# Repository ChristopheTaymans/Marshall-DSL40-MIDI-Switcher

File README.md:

# MIDI switcher for Marshall DSL 40

## Introduction
This repository propose a DYI switcher for the Marshall DSL40 tube Amplificator. The switcher is capable to select channel 1 / 2 selection with switching between modes ( Clean/Crunch / OD1 /OD 2 ). It can select also Master 1 or 2 and the FX loop activation/deactivation.

The core of the circuit is an **Arduino Every**. 
The switcher is linked with the DSL40 through a MIDI cable ( DIN5 )  and is powered up with an external 9V source.
the switching command is provided by 4 momentary footswitches. 
- Footswitch 1 is for clean/crunch switching ( and implicitely for channel 1 activation): Two leds indicate the clean/crunch status
- Footswitch 2 is for OD1/OD2switching ( and implicitely for channel 2 activation ) : Two leds indicate the OD1/OD2 status
- Footswitch 3 is for Master 1 / Master 2 switching : Two leds indicate the Mastezr 1 / 2 status
- Footswitch 4 is FX loop activation/deactivation : one led indicates the FX loop status.

***Short demo video at https://youtu.be/Z-kX9PDRV-0***

## Synchronisation function

The "issue" with DSL40 is that there is no MIDI messages sent back by the amp. to the switcher to give the current status of all presets.
Each modes ( clean/crunch/OD1/OD2) have their own presets regarding FX loop and Master. Combination of presets might become a bit complex and lead to a de-synchronisation.
So, each time the switcher is turned on, the amp. preset must be manually synchronised with the switcher preset state ( leds ). Also, if a preset is modified manually during a use session, the switcher is desyncronised with the amp.
With most of the DYI switcher that I've seen on the web, the manual (re)synchronisation is a must to keep both switcher and amp. on the same state.

This switcher program have an integrated syncrhonisation function. The switcher presets states are stored in the EEPROM. So, each time the switcher is turned on, its last state is restored. 
if the amp presets has been modified manually in the mean time, a synchronisation of the amps can be triggered by a long hold ( > 3 sec. ) on the clean/crunch footswitch.

In a first version of the program, the synchronisation was triggered each time the switcher was turned on. Finally, the synchro is only triggered by demand.

## Hardware 

In the folder Eagle, you'll find schematic and board implementation to build the circuit board. 
If you have a CNC machine, you'll find the G code files to engrave the circuit and the case.

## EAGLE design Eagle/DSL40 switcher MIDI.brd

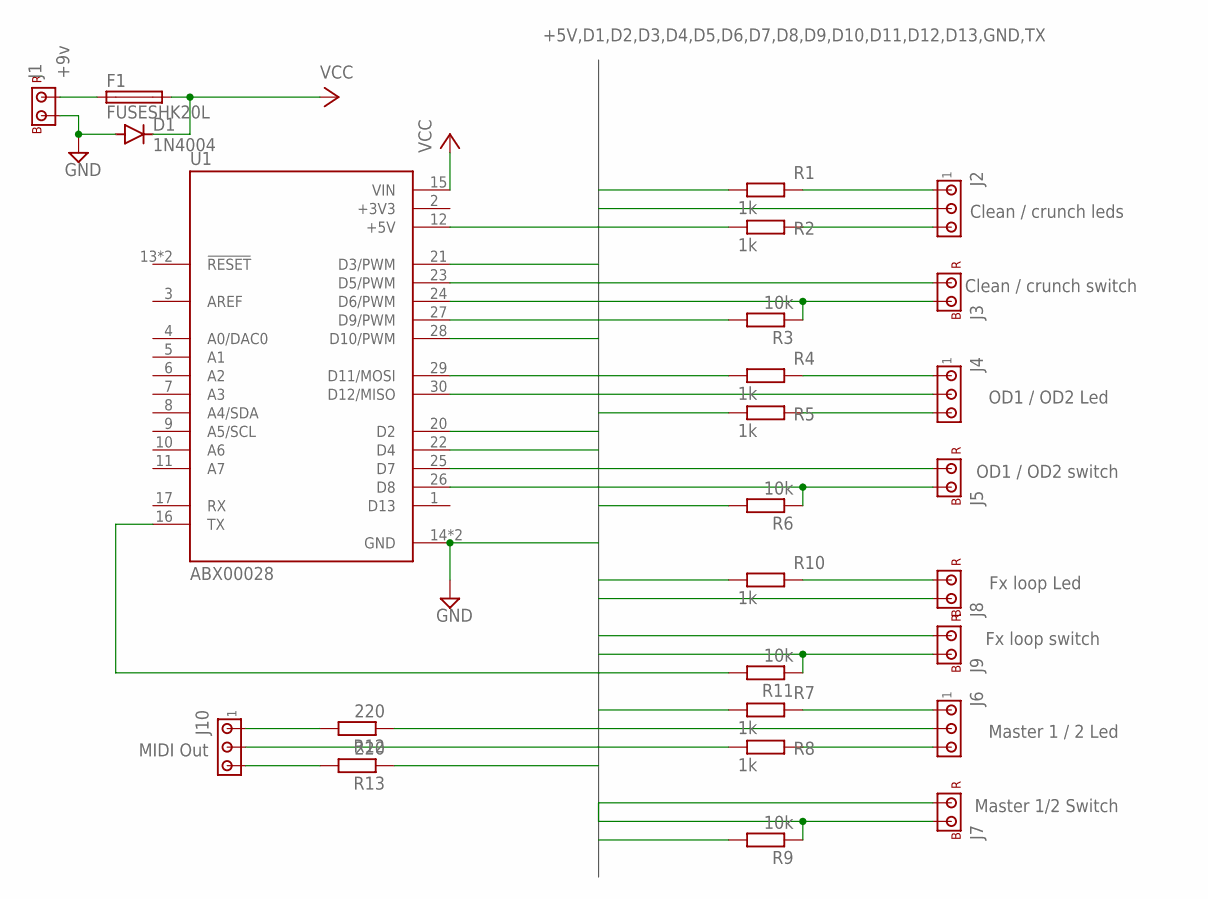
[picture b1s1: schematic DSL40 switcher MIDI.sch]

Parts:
D1: 1N4004; DO41-10
F1: FUSESHK20L; SHK20L
J1: +9v; CONNECTOR-JST-2-2.54
J2: Clean / crunch leds; CONNECTOR-JST-3-2.54
J3: Clean / crunch switch; CONNECTOR-JST-2-2.54
J4: OD1 / OD2 Led; CONNECTOR-JST-3-2.54
J5: OD1 / OD2 switch; CONNECTOR-JST-2-2.54
J6: Master 1 / 2 Led; CONNECTOR-JST-3-2.54
J7: Master 1/2 Switch; CONNECTOR-JST-2-2.54
J8: Fx loop Led; CONNECTOR-JST-2-2.54
J9: Fx loop switch; CONNECTOR-JST-2-2.54
J10: MIDI Out; CONNECTOR-JST-3-2.54
R1, R2, R4, R5, R7, R8, R10: 1k; 0207/10
R3, R6, R9, R11: 10k; 0207/10
R12, R13: 220; 0207/10
U1: ABX00028; MODULE_ABX00028

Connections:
+3V3: U1.2 (+3V3)
+5V: J3.RED, J5.RED, J7.RED, J9.RED, R12.1, U1.12 (+5V)
D2: J3.BLACK, R3.1, U1.20 (D2)
D3: R2.1, U1.21 (D3/PWM)
D4: R1.1, U1.22 (D4)
D5: J5.BLACK, R6.1, U1.23 (D5/PWM)
D6: R5.1, U1.24 (D6/PWM)
D7: R4.1, U1.25 (D7)
D8: J7.BLACK, R9.1, U1.26 (D8)
D9: R8.1, U1.27 (D9/PWM)
D10: R7.1, U1.28 (D10/PWM)
D11: R10.1, U1.29 (D11/MOSI)
D12: J9.BLACK, R11.1, U1.30 (D12/MISO)
GND: D1.A, J1.BLACK, J2.BLACK (2), J4.BLACK (2), J6.BLACK (2), J8.BLACK, J10.BLACK (2), R3.2, R6.2, R9.2, R11.2, U1.14 (GND), U1.19 (GND)
unnamed: J2.YELLOW (3), R2.2
unnamed: J2.RED (1), R1.2
unnamed: J4.YELLOW (3), R5.2
unnamed: J4.RED (1), R4.2
unnamed: J8.RED, R10.2
unnamed: J6.RED (1), R7.2
unnamed: J6.YELLOW (3), R8.2
unnamed: J10.RED (1), R12.2
unnamed: J10.YELLOW (3), R13.2
unnamed: F1.1A (1), J1.RED
TX: R13.1, U1.16 (TX)
VCC: D1.C, F1.2A (2), U1.15 (VIN)

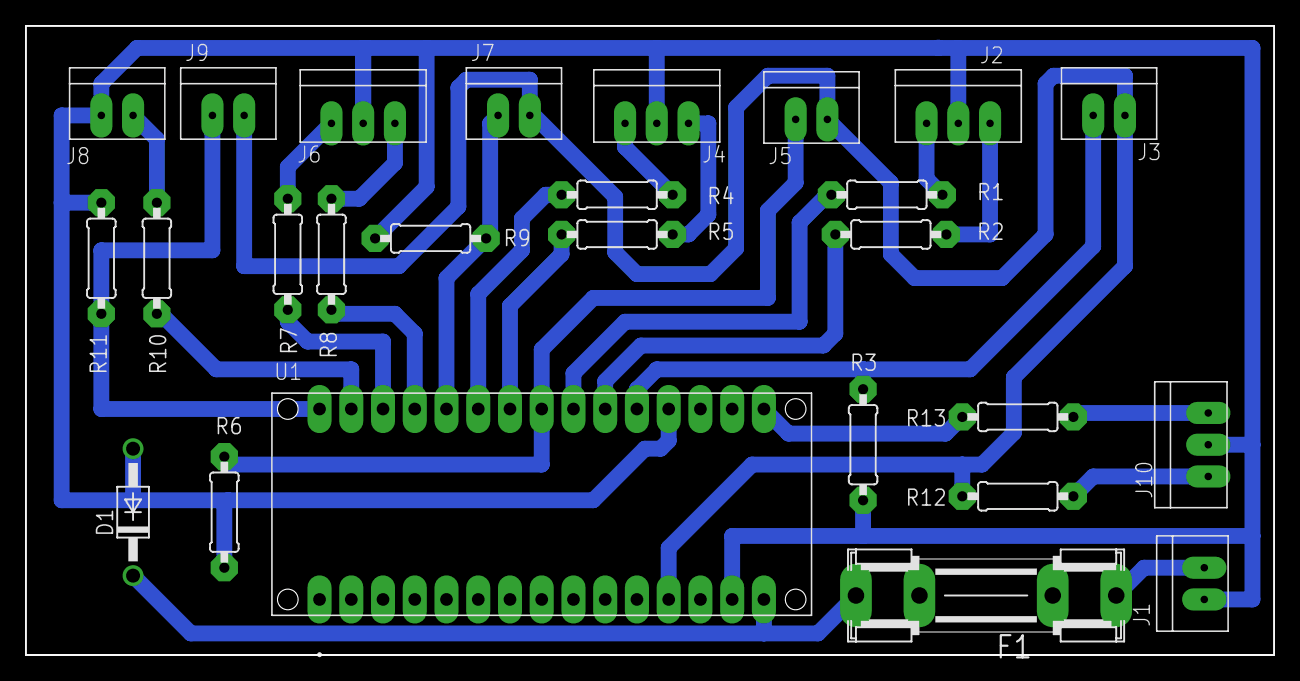
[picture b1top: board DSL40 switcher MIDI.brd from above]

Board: 2 copper layers, 99.9 x 50.3 mm, 26 parts (0 on the bottom side), 25 nets.

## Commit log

2025-12-12 Add README for MIDI switcher project
    Add detailed documentation for MIDI switcher project, including introduction, functionality, and synchronization features.
2025-12-12 Create tes
2025-12-12 Implement MIDI switcher for Marshall DSL 40
    This code implements a MIDI switcher for the Marshall DSL 40 amplifier, allowing control over various channels and features through footswitches. It includes functionality for state synchronization w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
2025-12-12 Create dummy
2025-12-12 Enhance README with hardware details and images
    Added hardware section with schematic and G code files.
2025-12-12 Add demo video link to README
    Added a short demo video link to the README.
2025-12-12 Fix spelling errors and enhance README clarity
    Corrected spelling of 'Synchronization' and improved clarity in hardware section.
